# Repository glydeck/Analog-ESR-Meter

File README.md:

-----------------------------------------------
# Analog ESR Meter
## Created with KiCAD, OpenSCAD, & Inkscape
#### Posted by glydeck 9/12/2024
-----------------------------------------------

## Introduction
This ESR Meter is an updated version of two articles written by me for Elektor Magazine.

- [**Elektor**](https://www.elektormagazine.com/)
- [**A Simple Analog ESR Meter**](https://www.elektormagazine.com/labs/a-simple-analog-esr-meter)
- [**My First PCB**](https://www.elektormagazine.com/magazine/elektor-261/60678)

The ESR Meter is basically an AC Ohmmeter with special scales and protective circuitry. It provides a continuous reading of series resistance in electrolytic capacitors. It operates at 100 kHz to keep the capacitive reactance factor near zero. The remaining series resistance is due to the electrolyte between the capacitor plates and indicates the state of dryness. Capacitor termination problems also show up plainly due to the continuous ohmic reading.

Additional information including parts list, schematic and circuit description can be found in the file **ESR Meter Manual.pdf** which is included in this repository.

## Requirements to Make your Own ESR Meter
Versions of the following programs:
- [**KiCad EDA**](https://www.kicad.org/)
- [**OpenSCAD**](https://openscad.org/)
- [**Inkscape**](https://github.com/inkscape/inkscape)
- [**The files in this repository**](https://github.com/glydeck/Analog-ESR-Meter)
## Contents

```
    README.md                -This document
    ESR Meter Manual.pdf     -Details for using the meter
    ESR_Box-OpenSCAD         -OpenSCAD code for the meter case
    ESR_Box-STL              -3D printable files for the case
    ESR_Meter_KicadProject   -KiCad project for circuit board
    ESR_MeterScale           -SVG file for the meter scale
    ESR_resources            -Various PDF files
    images                   -Images used throughout the project
```
### KiCad Project

##### 3D KiCad Rendering

This project uses a depreciated version of KiCad (Version 5.0.2-5 Mac OSX). At some point in the future I hope to update this to a newer version. For now the files for making the PCB are open source on OSH Park.  Boards can be ordered directly from them as well.
- [**OSH Park ESR Meter Boards**](https://oshpark.com/shared_projects/dSvuQNhP)

##### PCB Top View

##### PCB Bottom View

## Meter Case

##### Meter Case Rendered in Blender

I found the OpenSCAD code for the case on Thingverse:
- [**Thingverse-Ultimate Box Maker**](https://www.thingiverse.com/thing:2938921)

The original code and conncept can be traced back to the French Blog **Hearty GFX**: 
- [**Hearty GFX**](http://heartygfx.blogspot.com/2016/01/the-ultimate-box-maker.html)
 
The code has been maintained and improved on by Joel Ebel on GitHub:
- [**GitHub-Ultimate Box Maker**](https://github.com/jbebel/Ultimate-Box-Maker)

The **Box Maker** code does not accomidate adding holes to the top or bottom of the case.  It also does not accomidate custom geometries, such as the battery holder, being added to the inside of the box.

In the OpenScad file **ESR_Box_all.scad** the extra holes in the top of the case and battery holder are included at the end of the file. These added geometries including holes for the meter, potentiometer, added battery cage are included starting on line 419.  The Battery holder runs from line 432 to line 487. The holes for the meter, switch and text are difference geometries subtracted from the case. This code runs from line 496 thru line 569.

##### Meter Case Rendered in OpenSCAD

### STL Files

There are two sets of STL files that are 3D printer ready.  I used Cura to generate the the G-Code for my printer and printed the case with a Creality Ender Model 3 printer.

The version one folder has a seperate bracket to help hold the 9 volt battery in place.  This piece would need to be glued in place on the bottom shell wall.

The version two folder this bracket is integral to the print of the bottom shell of the case.

## Meter Scale
The Meter scale graphic was created using **Inkscape**.  

## Assembly of ESR Meter
The meter is very easy to assemble.  After stuffing the Printed Circuit Board with components wires can be attached to to the PCB.  These wires can then be attached to the components in the case.  That includes potentiometer with integrated on/off switch, the binding posts and the 9V battery clip.  Two images are provided to show those connections.  When completed the PCB can be turned over and bolted to the back of the meter.  The meter acts as a holding device for the circuit board.

#### Stuffed Board

#### Wiring to Potentiometer, Binding Posts, & Battery Clip

#### Closer View of Internal Wiring

#### Board Attached to the Meter

### ESR Resources
Description of included PDF files relevant to this project:

- Insert Analog_Panel_Meter.pdf - **Meter Cutout**
- sboa068.pdf - **Burr Brown App Note Absolute Value Circuits**
- Schmitt_Trigger_Oscillators.pdf - **Schmitt Trigger Oscillators**
- snoa998.pdf - **Texas Instruments App Note Relaxation oscillator circuit**
- US4216424.pdf - **Untited States Patent for an ESR Meter**
- US6677764.pdf - **United States Patent for Protecting Test Equipment**

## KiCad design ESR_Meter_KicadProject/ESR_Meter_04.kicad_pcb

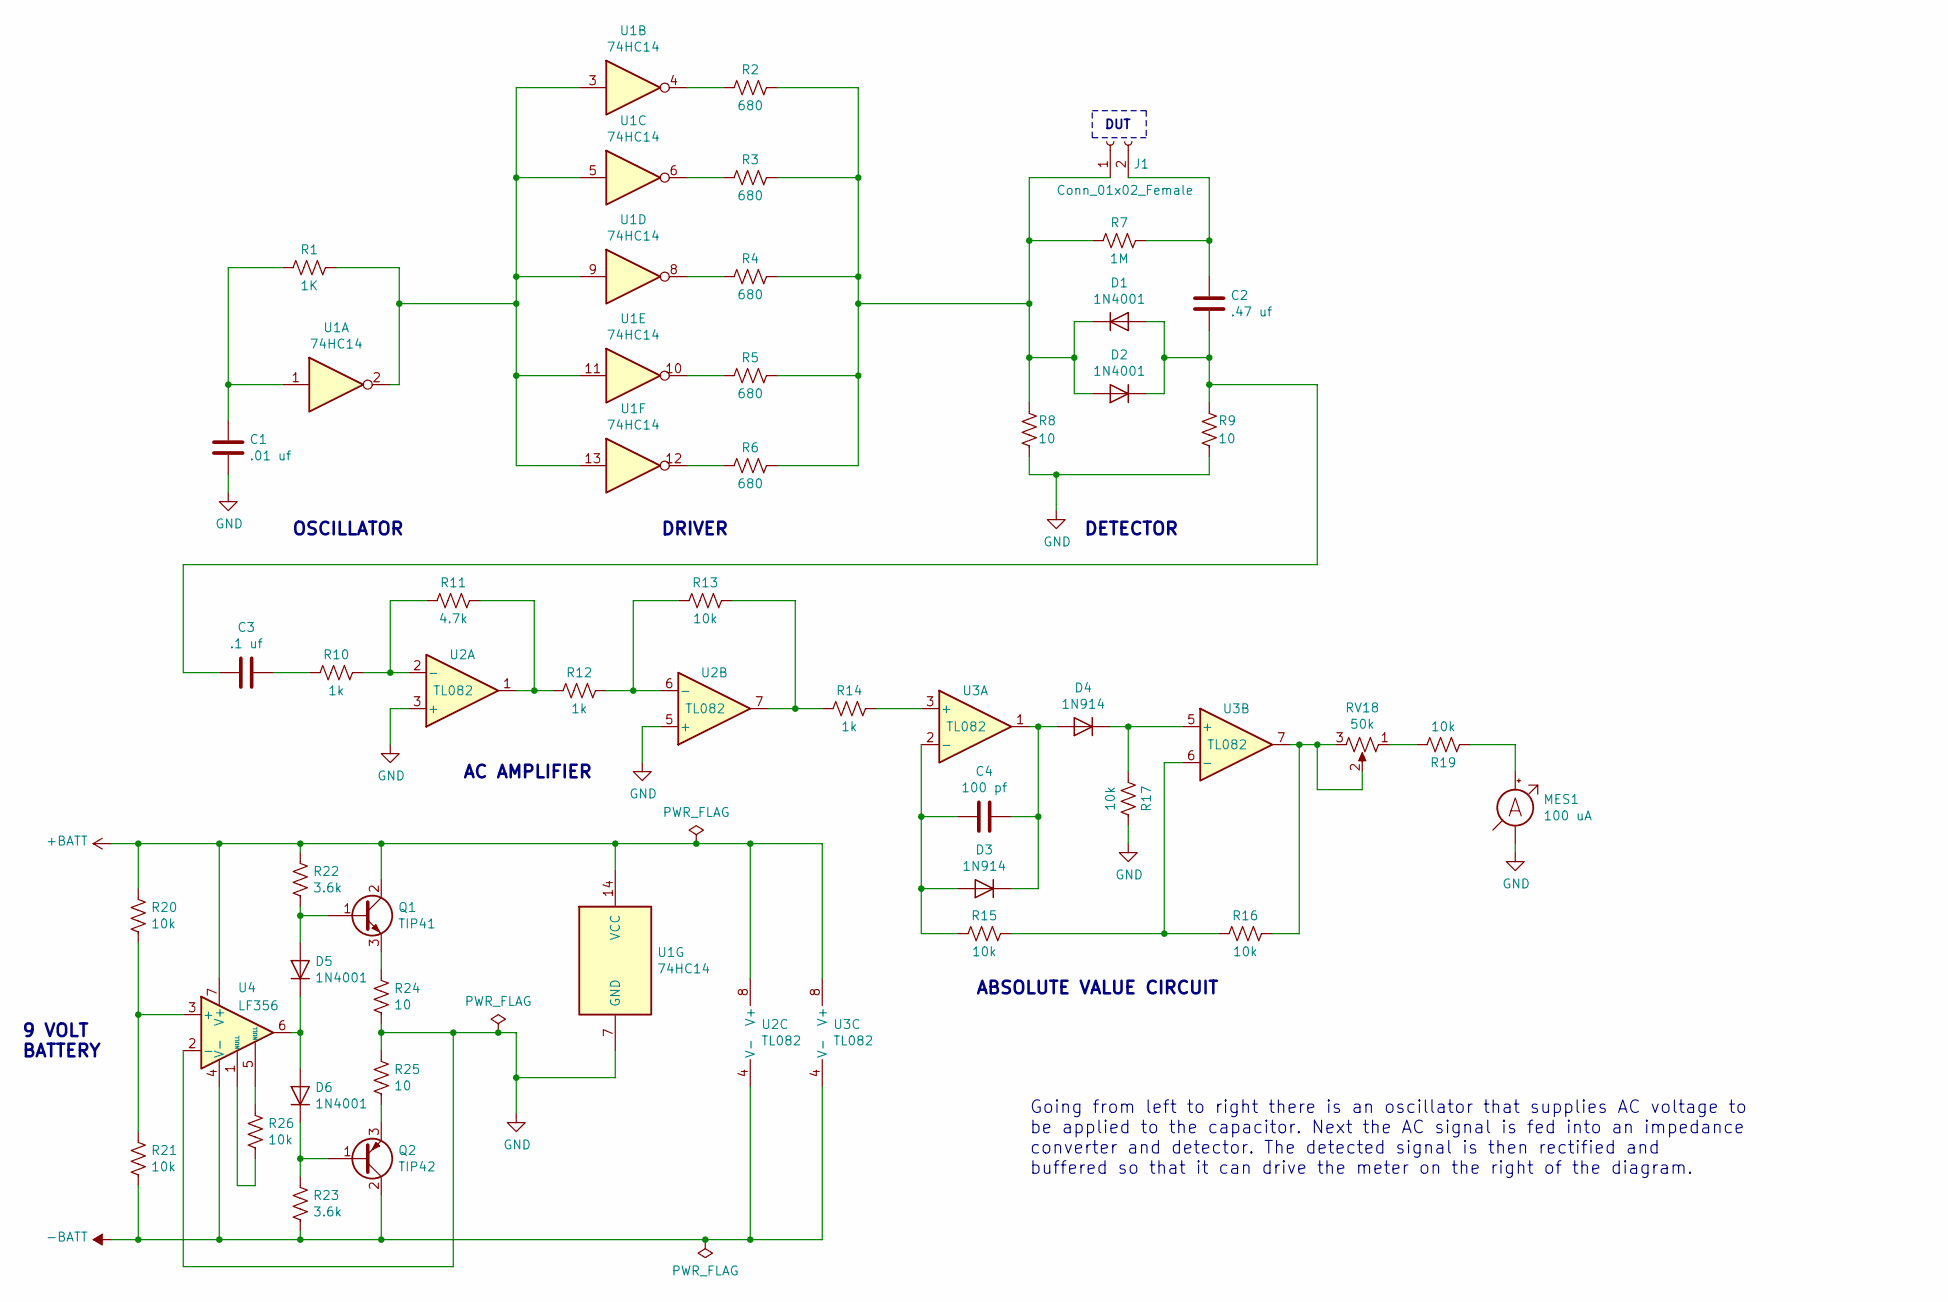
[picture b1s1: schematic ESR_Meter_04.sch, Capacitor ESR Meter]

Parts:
C1: .01 uf; C_Disc_D10.0mm_W2.5mm_P5.00mm
C2: .47 uf; C_Rect_L41.5mm_W13.0mm_P37.50mm_MKS4
C3: .1 uf; C_Disc_D10.0mm_W2.5mm_P5.00mm
C4: 100 pf; C_Disc_D7.0mm_W2.5mm_P5.00mm
D1, D2, D5, D6: 1N4001; D_DO-41_SOD81_P10.16mm_Horizontal
D3, D4: 1N914; D_DO-35_SOD27_P7.62mm_Horizontal
J1: Conn_01x02_Female; SolderWirePad_1x02_P7.62mm_Drill2mm
MES1: 100 uA; Analog Meter
Q1: TIP41; TO-220-3_Vertical
Q2: TIP42; TO-220-3_Vertical
R1: 1K; R_Axial_DIN0207_L6.3mm_D2.5mm_P10.16mm_Horizontal
R2, R3, R4, R5, R6: 680; R_Axial_DIN0207_L6.3mm_D2.5mm_P10.16mm_Horizontal
R7: 1M; R_Axial_DIN0207_L6.3mm_D2.5mm_P10.16mm_Horizontal
R8, R9, R24, R25: 10; R_Axial_DIN0207_L6.3mm_D2.5mm_P10.16mm_Horizontal
R10, R12, R14: 1k; R_Axial_DIN0207_L6.3mm_D2.5mm_P10.16mm_Horizontal
R11: 4.7k; R_Axial_DIN0207_L6.3mm_D2.5mm_P10.16mm_Horizontal
R13, R15, R16, R17, R19, R20, R21: 10k; R_Axial_DIN0207_L6.3mm_D2.5mm_P10.16mm_Horizontal
R22, R23: 3.6k; R_Axial_DIN0207_L6.3mm_D2.5mm_P10.16mm_Horizontal
R26: 10k; R_Axial_DIN0207_L6.3mm_D2.5mm_P2.54mm_Vertical
RV18: 50k; Potentiometer_Bourns_3266Y_Vertical
U1: 74HC14; DIP-14_W7.62mm_Socket_LongPads
U2, U3: TL082; DIP-8_W7.62mm_Socket_LongPads
U4: LF356; DIP-8_W7.62mm_Socket_LongPads

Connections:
+BATT: Q1.2 (C), R20.1, R22.1, U1.14 (VCC), U2.8 (V+), U3.8 (V+), U4.7 (V+); also elsewhere on the board
-BATT: Q2.2 (C), R21.2, R23.2, U2.4 (V-), U3.4 (V-), U4.4 (V-); also elsewhere on the board
GND: C1.1, MES1.1 (-), R8.1, R9.1, R17.1, R24.2, R25.1, U1.7 (GND), U2.3 (+), U2.5 (+), U4.2 (-); also elsewhere on the board
unnamed: C1.2, R1.2, U1.1
unnamed: C2.1, C3.2, D1.2 (A), D2.1 (K), R9.2
unnamed 5: C2.2, J1.2, R7.1; also elsewhere on the board
unnamed: C3.1, R10.2
unnamed: C4.1, D3.1 (K), D4.2 (A), U3.1
unnamed: C4.2, D3.2 (A), R15.2, U3.2 (-)
unnamed 9: D1.1 (K), D2.2 (A), J1.1, R2.1, R3.1, R4.1, R5.1, R6.1, R7.2, R8.2; also elsewhere on the board
unnamed: D4.1 (K), R17.2, U3.5 (+)
unnamed: D5.1 (K), D6.2 (A), U4.6
unnamed: D5.2 (A), Q1.1 (B), R22.2
unnamed: D6.1 (K), Q2.1 (B), R23.1
unnamed 14: MES1.2 (+), R19.2; also elsewhere on the board
unnamed: Q1.3 (E), R24.1
unnamed: Q2.3 (E), R25.2
unnamed: R1.1, U1.2, U1.3, U1.5, U1.9, U1.11, U1.13
unnamed: R2.2, U1.4
unnamed: R3.2, U1.6
unnamed: R4.2, U1.8
unnamed: R5.2, U1.10
unnamed: R6.2, U1.12
unnamed: R10.1, R11.2, U2.2 (-)
unnamed: R11.1, R12.2, U2.1
unnamed: R12.1, R13.2, U2.6 (-)
unnamed: R13.1, R14.2, U2.7
unnamed: R14.1, U3.3 (+)
unnamed: R15.1, R16.2, U3.6 (-)
unnamed: R16.1, RV18.2, RV18.3, U3.7
unnamed: R19.1, RV18.1
unnamed: R20.2, R21.1, U4.3 (+)
unnamed: R26.1, U4.5 (NULL)
unnamed: R26.2, U4.1 (NULL)

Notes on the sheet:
DUT
OSCILLATOR
DRIVER
DETECTOR
AC AMPLIFIER
ABSOLUTE VALUE CIRCUIT
Going from left to right there is an oscillator that supplies AC voltage to be applied to the capacitor. Next the AC signal is fed into an impedance converter and detector. The detected signal is then rectified and buffered so that it can drive the meter on the right of the diagram.
9 VOLT BATTERY

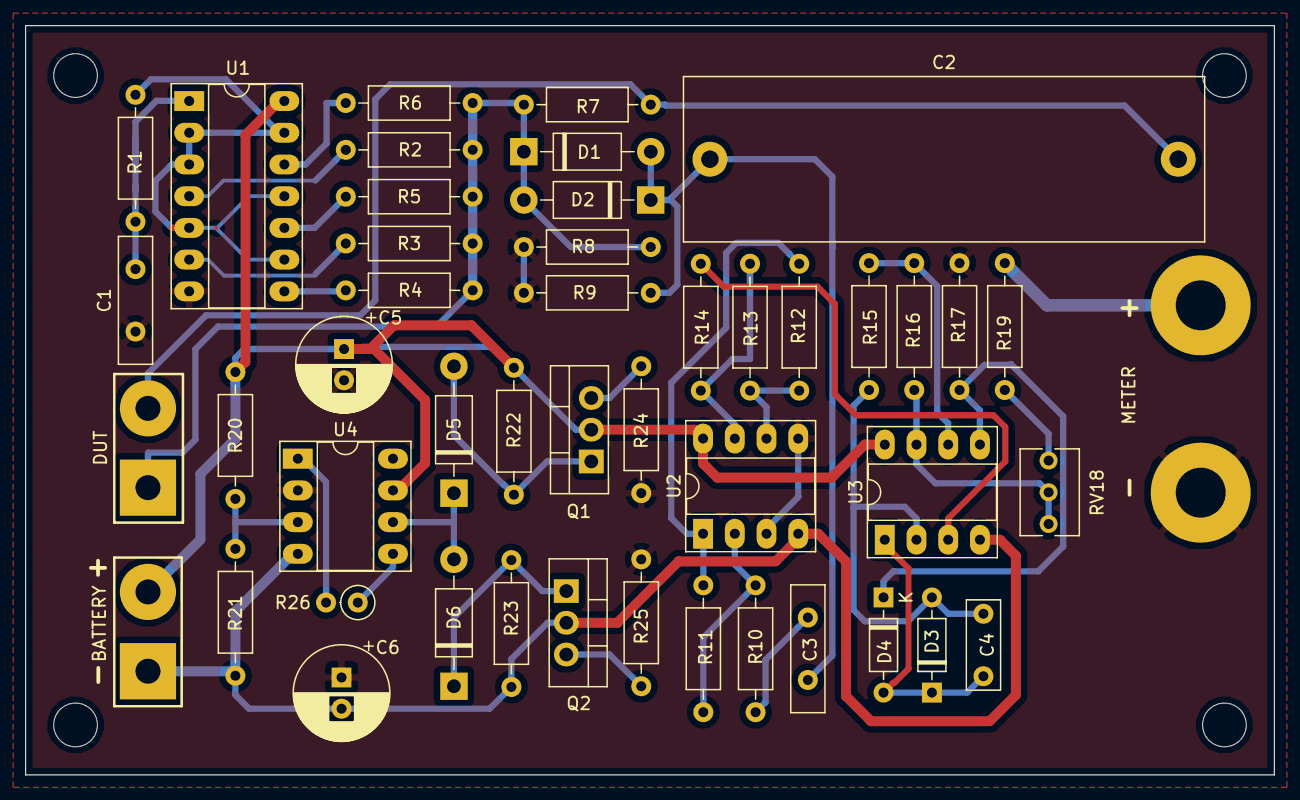
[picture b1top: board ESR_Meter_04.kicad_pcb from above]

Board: 2 copper layers, 100.0 x 60.0 mm, 47 parts (0 on the bottom side), 34 nets.

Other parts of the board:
BATTERY: Conn_01x02_Female; SolderWirePad_1x02_P7.62mm_Drill2mm
C5, C6: CP_Radial_D7.5mm_P2.50mm
DUT: Conn_01x02_Female; SolderWirePad_1x02_P7.62mm_Drill2mm
METER: 500 uA; Analog Meter

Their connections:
+BATT: BATTERY.2, C5.1; also elsewhere on the board
-BATT: BATTERY.1, C6.2; also elsewhere on the board
GND: C5.2, C6.1, METER.1; also elsewhere on the board
unnamed 5: DUT.2; also elsewhere on the board
unnamed 9: DUT.1; also elsewhere on the board
unnamed 14: METER.2; also elsewhere on the board

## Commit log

2024-09-17 Update README.md
    Added STL Details
2024-09-17 Update README.md
    Added image of OpenSCAD render
2024-09-17 Update README.md
    Added Elektor Magazine information
